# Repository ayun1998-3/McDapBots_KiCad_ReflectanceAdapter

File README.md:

# McDap Bots Pedagogical Robot

This project was created as a capstone project for the University of Virginia Department of Electrical and Computer Engineering. Our goal was to create a small robot which could be programmed by students, for use as a teaching aide in an embedded systems course. This repository contains the software component of this, both drivers and application code.

**Authors**
- Colby Wise
- Pratik Pandit
- Austen Yun 
- David Merino
- Marc Rosenthal

**Advisors**: Todd DeLong and Adam Barnes 

**Features at a glance**
- 2 motors (PWM controlled), OLED screen (I2C), reflectance sensor (I2C), bump switches (GPIO), Bluetooth (UART), and infrared sensors (ADC)
- battery charging port and battery voltage display (press button to enable)
- support for TI and STM microcontrollers

## What is contained here
This repository contains a KiCad project file for the reflectance sensor adapter board, which connects the [15-Channel Reflectance Sensor Array](https://www.pololu.com/product/4315) to
the robot's main PCB. The reflectance sensor board can be soldered onto this adapter board via male header pins, and this adapter board has pins that plug into the bottom of the main PCB.

**Schematic File**

KiCad schematic file that shows the electrical connections of the reflectance sensor adapter board. 

**Layout File**

KiCad layout file that shows how the components are placed and routed on the reflectance sensor adapter board.

**Bill of Materials Files**

BOM.xlsx contains a list of all the parts needed for to add the reflectance sensor as a feature to the robot.
Digikey_Parts_List.xlsx can be uploaded to Digikey to select the parts needed for one copy of this board.

## How to use this repository
1. Copy the repository locally to your computer
2. Using KiCad 8.0 (or higher version) open the file `Reflectance_Adapter.kicad_pro"`
3. Generate necessary gerber files and order components

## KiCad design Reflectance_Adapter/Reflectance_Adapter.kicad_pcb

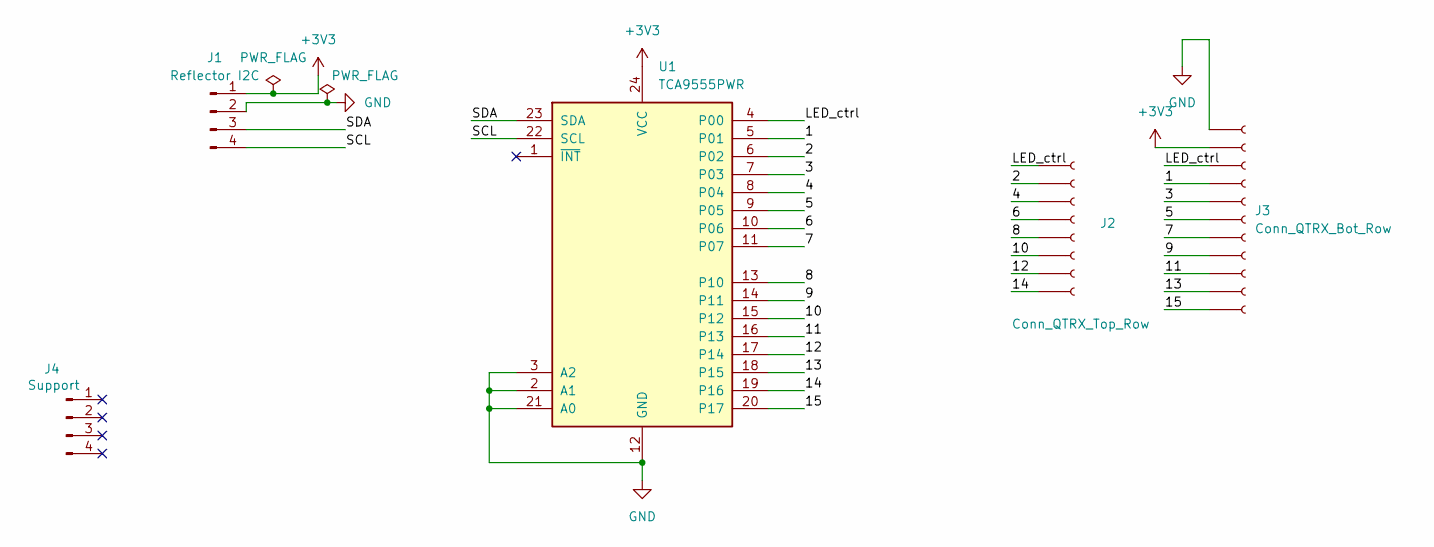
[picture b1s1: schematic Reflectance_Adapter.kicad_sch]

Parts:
J1: Reflector I2C; PinHeader_1x04_P2.54mm_Vertical
J2: Conn_QTRX_Top_Row; PinSocket_1x08_P2.54mm_Vertical
J3: Conn_QTRX_Bot_Row; PinSocket_1x11_P2.54mm_Vertical
J4: Support; PinHeader_1x04_P2.54mm_Vertical
U1: TCA9555PWR; TSSOP-24_4.4x7.8mm_P0.65mm

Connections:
+3V3: J1.1, J3.2, U1.24 (VCC)
/1: J3.4, U1.5 (P01)
/2: J2.2, U1.6 (P02)
/3: J3.5, U1.7 (P03)
/4: J2.3, U1.8 (P04)
/5: J3.6, U1.9 (P05)
/6: J2.4, U1.10 (P06)
/7: J3.7, U1.11 (P07)
/8: J2.5, U1.13 (P10)
/9: J3.8, U1.14 (P11)
/10: J2.6, U1.15 (P12)
/11: J3.9, U1.16 (P13)
/12: J2.7, U1.17 (P14)
/13: J3.10, U1.18 (P15)
/14: J2.8, U1.19 (P16)
/15: J3.11, U1.20 (P17)
/LED_ctrl: J2.1, J3.3, U1.4 (P00)
/SCL: J1.4, U1.22 (SCL)
/SDA: J1.3, U1.23 (SDA)
GND: J1.2, J3.1, U1.2 (A1), U1.3 (A2), U1.12 (GND), U1.21 (A0)

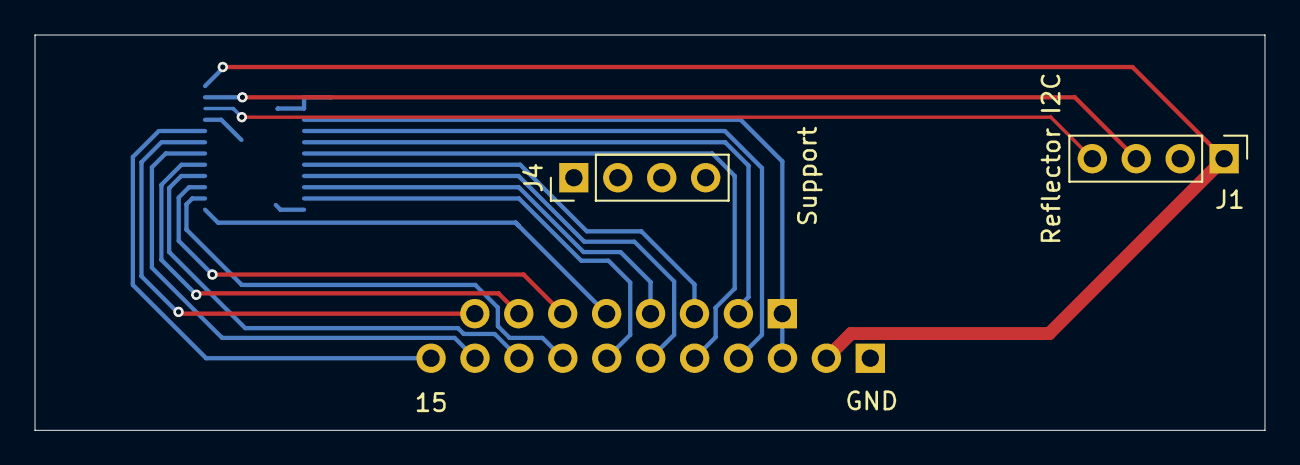
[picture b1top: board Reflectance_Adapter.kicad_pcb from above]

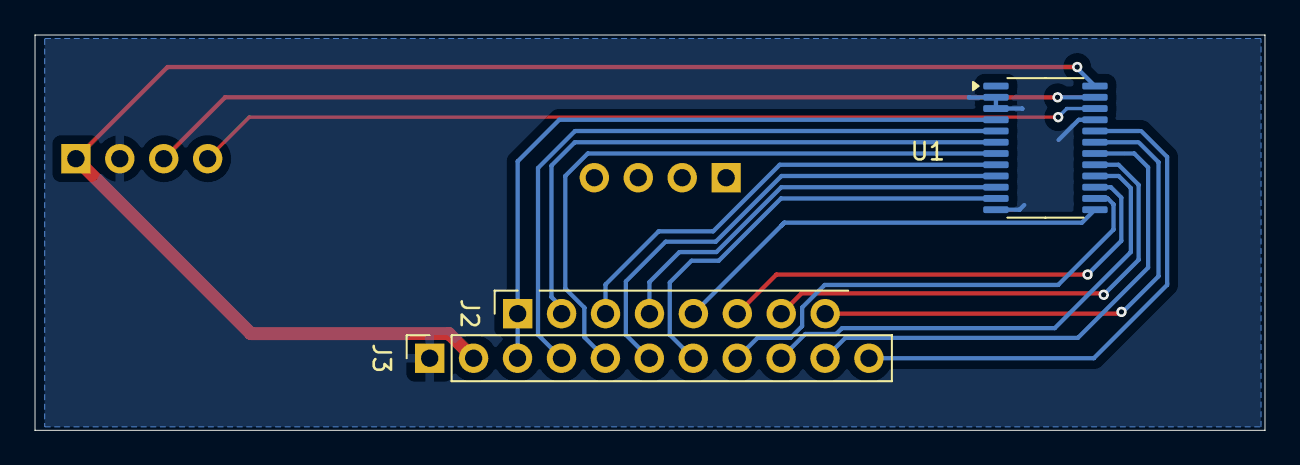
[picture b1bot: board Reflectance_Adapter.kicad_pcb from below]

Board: 2 copper layers, 71.1 x 22.9 mm, 5 parts (3 on the bottom side), 20 nets.

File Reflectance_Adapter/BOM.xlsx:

Reflectance Sensor Adapter Board Parts
Id | Designator | Footprint | Quantity | Designation | Supplier | Link | Notes
1 | J1, J4 | PinHeader_1x04_P2.54mm_Vertical | 2 | Reflector I2C, Support | Digikey | 0879370800 Molex | Connectors, Interconnects | DigiKey | Long 4-pin male header
2 | U1 | TSSOP-24_4.4x7.8mm_P0.65mm | 1 | TCA9555PWR | Digikey | TCA9555PWR Texas Instruments | Integrated Circuits (ICs) | DigiKey | GPIO to I2C expander
Id | Designator | Footprint | Quantity | Designation | Supplier | Link | Notes
1 | J2 | PinSocket_1x08_P2.54mm_Vertical | 1 | Conn_QTRX_Top_Row | Digikey | TSW-120-07-L-S Samtec Inc. | Connectors, Interconnects | DigiKey | 8-pin male header, soldered onto both reflectance sensor board and adapter board
2 | J3 | PinSocket_1x11_P2.54mm_Vertical | 1 | Conn_QTRX_Bot_Row | Digikey | TSW-120-07-L-S Samtec Inc. | Connectors, Interconnects | DigiKey | 11-pin male header, soldered onto both reflectance sensor board and adapter boa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
3 |  |  | 1 | QTRX-HD-15RC Reflectance Sensor Array | Pololu | Pololu - QTRX-HD-15RC Reflectance Sensor Array: 15-Channel, 4mm Pitch, RC Outpu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 | 15-Channel Reflectance Sensor Array Board from Pololu

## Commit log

2025-10-09 Created empty KiCad project
2025-10-09 Completed schematic
2025-10-09 Assigned footprints
2025-10-10 Completed layout
    User layer 1 contains dimensions of Pololu reflectance sensor array board. User layer 8 contains dimensions of slots of Pololu Chassis (copied over from the MSPM0 kicad project)
2025-10-15 Added text to silkscreen
    Also generated Gerbers
2025-12-03 corrected i2c pin positions
2025-12-18 Initialize README with project details and features
    Add project overview and usage instructions to README
2025-12-18 Added BOM and digikey parts list files
2025-12-18 Update README.md
    Update README.md with info about BOM and digikey parts list
2025-12-18 Closed kicad project
2025-12-18 Reformatted some files
